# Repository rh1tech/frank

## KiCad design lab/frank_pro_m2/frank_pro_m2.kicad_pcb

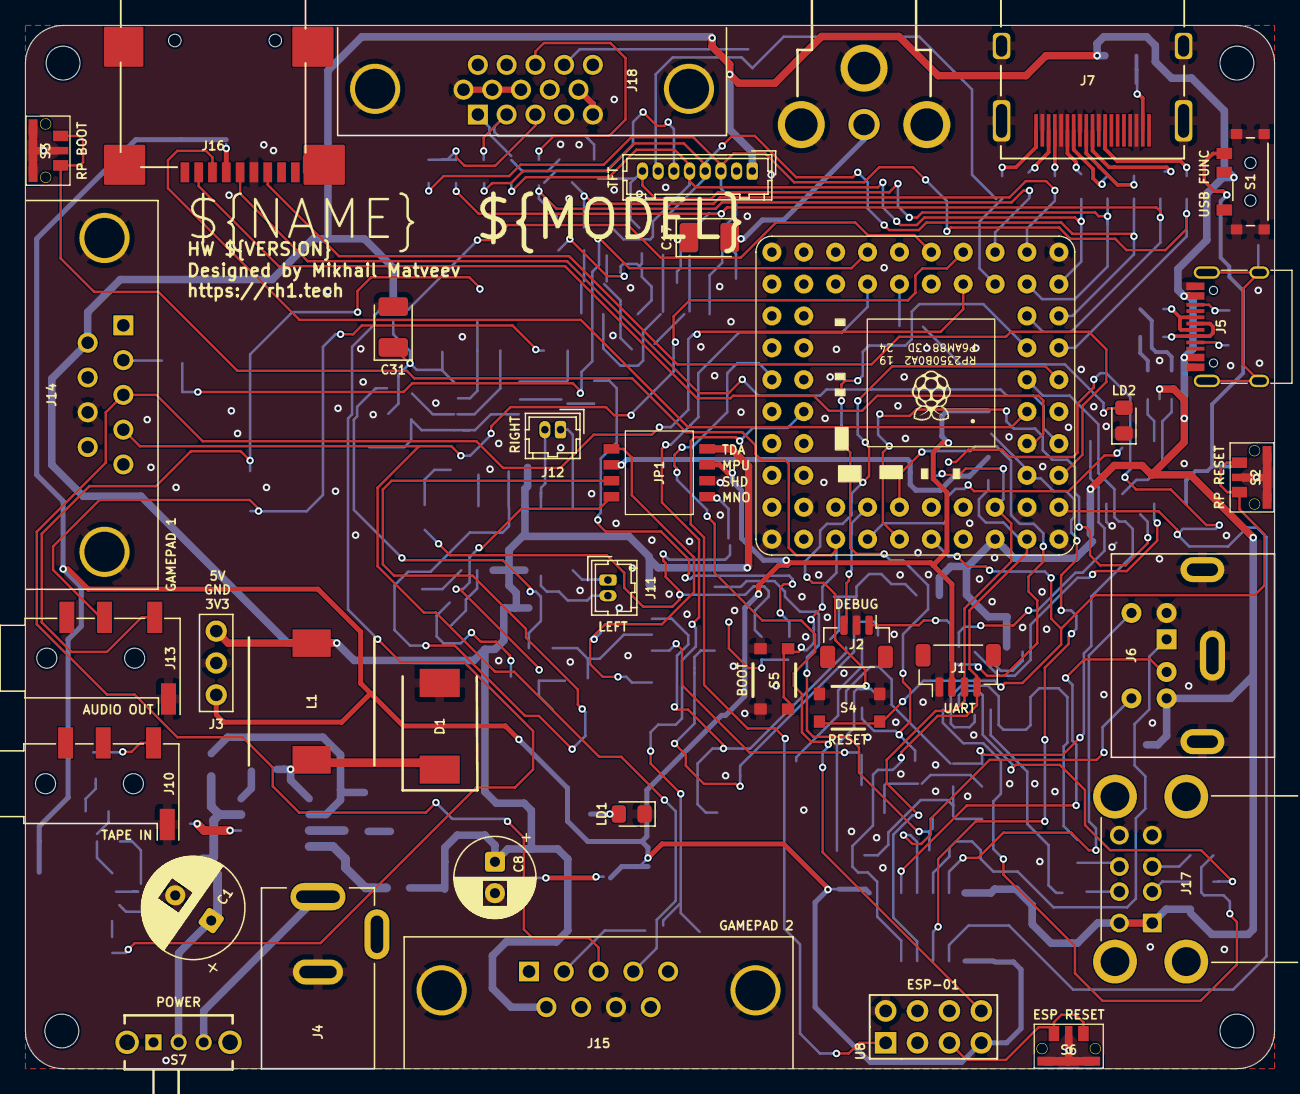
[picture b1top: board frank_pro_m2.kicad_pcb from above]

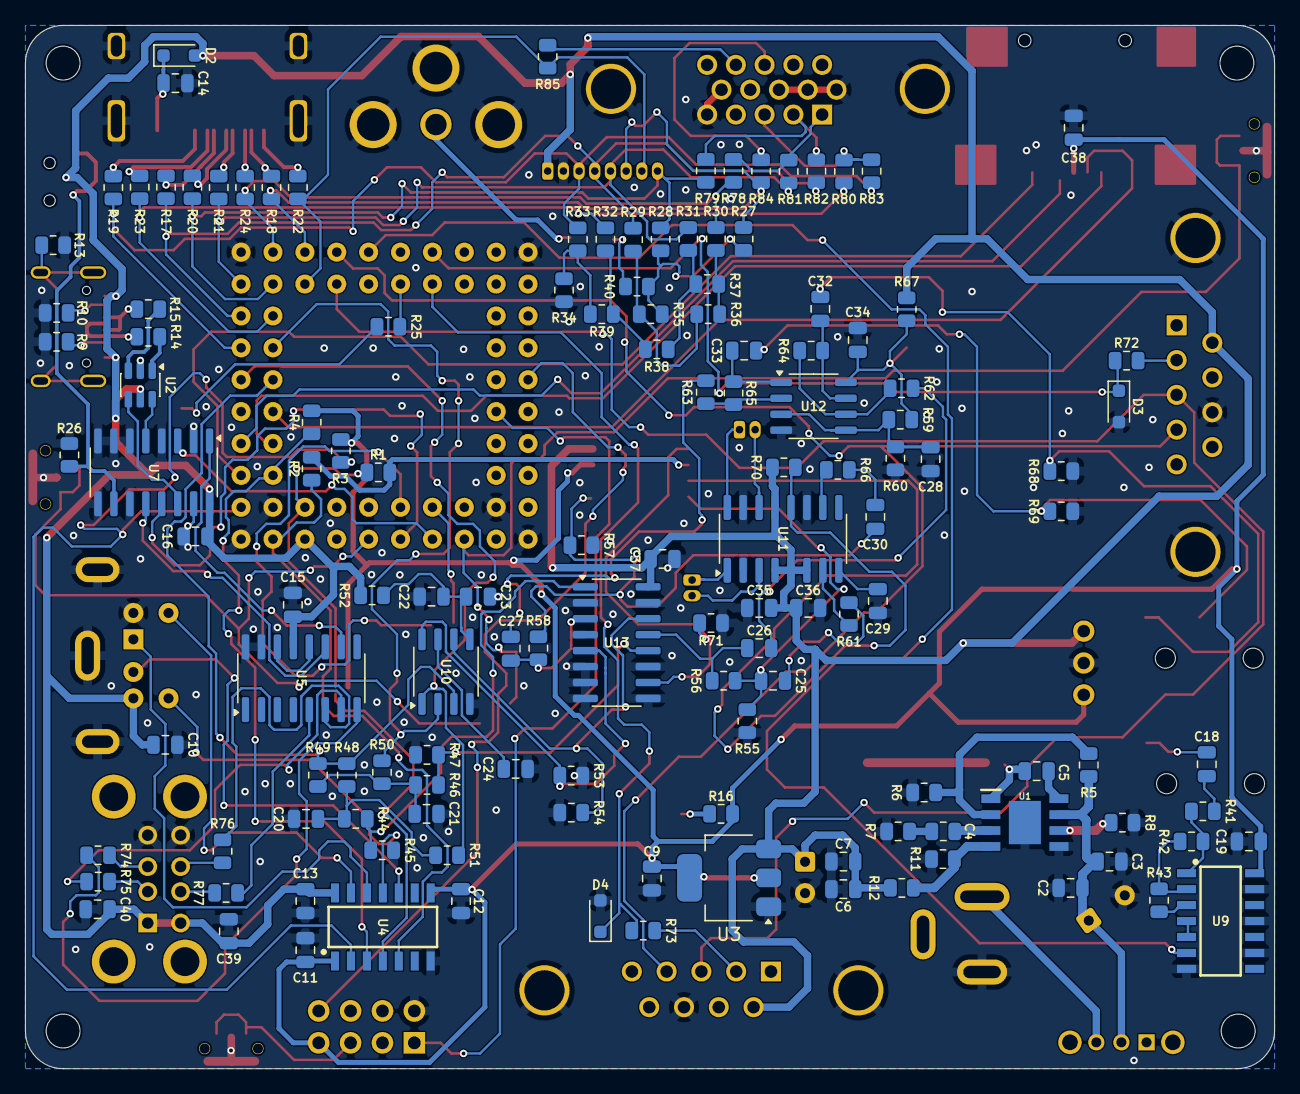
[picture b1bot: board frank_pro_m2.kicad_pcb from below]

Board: 2 copper layers, 99.5 x 83.1 mm, 175 parts (135 on the bottom side), 137 nets.

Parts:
C1: 680u; C_Radial_D8.0mm_P3.50mm
C2, C7, C9, C22, C24, C26, C27, C28, C32, C33, C39, C40: 10u; C_0805_2012Metric
C3, C5, C6, C10, C11, C12, C13, C14, C16, C18, C19, C23, C29, C34, C37, C38: 100n; C_0805_2012Metric
C4: 150pF; R_0805_2012Metric
C8: 220u; C_Radial_D6.3mm_P2.50mm
C15: 4.7u; C_0805_2012Metric
C17: 220u; C_3528_Tantalum
C20, C21: 47n; C_0805_2012Metric
C25, C30, C35: 1u; C_0805_2012Metric
C31: 10u; C_3528_Tantalum
C36: 47u; C_0805_2012Metric
D1: 1N5822; D_SMA_SS34
D2: 1N5819WS; D_SOD-323
D3, D4: 3V3; D_SOD-323
H1, H2, H3, H4: Hole 2.7mm; MountingHole_2.7mm
J1: UART; JST_SH_1x04_P1.00mm_Vertical
J2: DEBUG; JST_SH_1x03_P1.00mm_Vertical
J3: PWR; PinHeader_1x03_P2.54mm
J4: DC-005-5A-2.0; BarrelJack_DC-005
J5: USB4215-03-A; USB_C_Receptacle
J6: MDC-036; MiniDIN_6pin_Female
J7: DC3RX19JA2; HDMI_Female
J8: RCA-103; BarrelJack_RCJ-012
J9: Pin Header 1x08; JST_GH_1x08_P1.25mm
J10, J13: PJ-320D; AudioJack_3.5mm_PJ320D
J11: PAM L; JST_GH_1x02_P1.25mm
J12: PAM R; JST_GH_1x02_P1.25mm
J14, J15: GP2; DSUB-9_Male_TopMount
J16: 104031-0811; MicroSD_SMD_Long
J17: SS-52100-004; USB_A_Stacked
J18: VGA; DSUB-15_Female
JP1: Config Switches; DIPSwitch_4pos_DS05
L1: 22uH; Inductor_CDRH104RNP
LD1: Green; LED_0805
LD2: Blue; LED_0805
R1, R2, R3, R4, R26, R44, R46, R56, R58, R59, R60, R61, R62, R63, R66, R70, R71: 10K; R_0805_2012Metric
R5, R7, R8, R42, R43: 100K; R_0805_2012Metric
R6: 24K; R_0805_2012Metric
R9, R10: 5.1K; R_0805_2012Metric
R11: 8.2K; R_0805_2012Metric
R12: 43K; R_0805_2012Metric
R13: 1M; R_0805_2012Metric
R14, R15, R74, R75, R76, R77: 22R; R_0805_2012Metric
R16, R25, R50, R51, R72, R73, R81, R82, R83: 1K; R_0805_2012Metric
R17, R18, R19, R20, R21, R22, R23, R24, R28, R29, R30, R31, R32, R33: 270R; R_0805_2012Metric
R27: 750R; R_0805_2012Metric
R34: 300R; R_0805_2012Metric
R35, R36, R37, R38, R39: 150R; R_0805_2012Metric
R40: 51R; R_0805_2012Metric
R41: 4.7K; R_0805_2012Metric
R45, R47, R48, R49, R55, R57: 2K; R_0805_2012Metric
R52, R67, R84, R85: 100R; R_0805_2012Metric
R53, R54: 470R; R_0805_2012Metric
R64, R65: 47K; R_0805_2012Metric
R68, R69: 20K; R_0805_2012Metric
R78, R79, R80: 330R; R_0805_2012Metric
S1: MSK12C02; Switch_Slide_MSK12C02
S2: RP Reset; Button_SMD_TS1234VW
S3: RP BOOT; Button_SMD_TS1234VW
S4: RP Reset; Button_SMD_3x4x2mm
S5: RP BOOT; Button_SMD_3x4x2mm
S6: ESP Reset; Button_SMD_TS1234VW
S7: SK12D07VG3NS; Switch_Slide_SK12D07VG3NS
U1: MP1584EN-LF-Z; SOIC-9_P1.27mm
U2: USBLC6-2SC6; SOT-23-6
U3: AMS1117 3.3; SOT-223-3_TabPin2
U4: TXS0104EDR; SOIC-14_P1.27mm
U5: MW7211A; SOP-16_P1.27mm
U6: Pimoroni PGA2350; PGA2350
U7, U13: 74HC4052D; SOP-16_P1.27mm
U8: ESP-01v090; ESP-01S
U9: CD4069UBM; SOIC-14_P1.27mm
U10: TDA1387T; SO-8
U11: PAM8403D; SOP-16_P1.27mm
U12: LM358; SO-8

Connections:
+3V3: C9.1, C11.1, C12.1, C19.1, C38.2, J1.2, J3.1, J16.4 (VDD), JP1.4 (NO_2), R3.2, R4.2, R16.2, U3.2 (VO), U4.1 (VCCA), U4.8 (OE), U8.7 (VCC), U9.14 (VDD)
/AMP_L: C26.1, R56.1, U13.13 (1Z)
/AMP_R: C27.1, R58.1, U13.3 (2Z)
/AUDIOSW: JP1.1 (COM_1), R71.2, U13.10 (S0)
/Audio/AMP_OUTL: C32.2, J13.T, R68.2
/Audio/AMP_OUTR: C33.2, J13.R, R69.2
/Audio/AMP_PAM_OUTL_M: J11.2, U11.3 (-OUTL)
/Audio/AMP_PAM_OUTL_P: J11.1, U11.1 (+OUT_L)
/Audio/AMP_PAM_OUTR_M: J12.2, U11.14 (-OUT_R)
/Audio/AMP_PAM_OUTR_P: J12.1, U11.16 (+OUT_R)
/Composite/CVBS: C17.2, J8.1
/DM: U6.53 (USB_DM), U7.3 (2Z)
/DP: U6.54 (USB_DP), U7.13 (1Z)
/ESP_RST: S6.1, U8.5 (RST)
/ESP_RX: U6.40 (GP38), U8.8 (URXD)
/ESP_TX: U6.41 (GP39), U8.1 (UTXD)
/MONO_L: C25.1, JP1.7 (COM_4), R55.1, R56.2
/MONO_R: C30.1, JP1.8 (NO_4), R57.1, R58.2
/MSPUP3V3: JP1.3 (COM_2), R1.2, R2.2
/PBOOTSEL: S3.1, S5.1, S5.3, U6.51 (BOOTSEL)
/PGPIO0: J1.3, R1.1, U4.4 (A3), U6.61 (GP0)
/PGPIO1: J1.4, R2.1, U4.5 (A4), U6.62 (GP1)
/PGPIO2: R3.1, U4.2 (A1), U6.2 (GP2)
/PGPIO3: R4.1, U4.3 (A2), U6.3 (GP3)
/PGPIO4: J16.7 (DAT0), U6.4 (GP4)
/PGPIO5: J16.2 (DAT3/CD), U6.5 (GP5)
/PGPIO6: J16.5 (CLK), U6.6 (GP6)
/PGPIO7: J16.3 (CMD), U6.7 (GP7)
/PGPIO9: R48.1, R49.1, U6.9 (GP9), U10.3 (DATA)
/PGPIO10: R51.2, U6.10 (GP10), U10.1 (SCLK)
/PGPIO11: R50.2, U6.11 (GP11), U10.2 (LRCK)
/PGPIO12: J9.3, R19.2, R33.1, R83.1, U6.12 (GP12)
/PGPIO13: R23.2, R32.1, R80.1, U6.13 (GP13)
/PGPIO14: J9.4, R17.2, R29.1, R82.1, U6.14 (GP14)
/PGPIO15: J9.8, R20.2, R28.1, R79.1, U6.15 (GP15)
/PGPIO16: J9.5, R21.2, R31.1, R81.1, U6.16 (GP16)
/PGPIO17: R24.2, R30.1, R78.1, U6.17 (GP17)
/PGPIO18: J9.6, R18.2, R27.1, R84.2, U6.19 (GP18)
/PGPIO19: J9.7, R22.2, R85.2, U6.20 (GP19)
/PGPIO20: J14.4, J15.4, U6.21 (GP20)
/PGPIO21: J14.3, J15.3, U6.22 (GP21)
/PGPIO22: U6.23 (GP22), U9.6 (I=*C)
/PGPIO26: D3.1 (K), R72.1, U6.27 (GP26)
/PGPIO27: D4.1 (K), R73.1, U6.28 (GP27)
/PRUN: S2.1, S4.1, S4.3, U6.56 (RUN)
/PS2/KB_CLK_5V: J6.5, U4.13 (B1)
/PS2/KB_DATA_5V: J6.1, U4.12 (B2)
/PS2/MS_CLK_5V: J6.6, U4.11 (B3)
/PS2/MS_DATA_5V: J6.2, U4.10 (B4)
/PSWCLK: J2.1, U6.55 (SWCLK)
/PSWDIO: J2.3, U6.52 (SWDIO)
/PWM_L: R46.2, R47.1, U13.12 (1Y0)
/PWM_R: R44.2, R45.1, U13.1 (2Y0)
/Power/D+: J5.6 (DP1), J5.8 (DP2), R15.2
/Power/D-: J5.5 (DN2), J5.7 (DN1), R14.2
/Power/VBUS_IN: C1.1, C2.1, C3.1, R5.2, S7.2, U1.7 (VIN)
/SHND: JP1.5 (COM_3), R70.2, U11.12 (SHND)
/TC_DM: U2.6 (I/O1), U7.5 (2Y1)
/TC_DP: U2.4 (I/O2), U7.14 (1Y1)
/TDA_L: R54.2, U10.6 (A_LEFT), U13.14 (1Y1)
/TDA_R: R53.1, U10.8 (A_RIGHT), U13.5 (2Y1)
/Tape In/TAPE: C18.2, J10.T
/UH_DM1: R75.1, U5.7 (DM3)
/UH_DM2: R77.1, U5.5 (DM2)
/UH_DM_IN: U5.10 (DMU), U7.1 (2Y0)
/UH_DP1: R74.1, U5.8 (DP3)
/UH_DP2: R76.1, U5.6 (DP2)
/UH_DP_IN: U5.11 (DPU), U7.12 (1Y0)
/UM_SW: R26.2, S1.3, U7.10 (S0)
GND: C1.2, C2.2, C3.2, C6.1, C7.2, C8.2, C9.2, C10.2, C11.2, C12.2, C13.2, C14.2, C15.2, C16.1, C19.2, C20.2, C21.2, C22.2, C23.2, C24.2, C28.1, C29.2, C31.2, C34.1, C35.2, C36.2, C37.1, C38.1, C39.2, C40.2, D1.2 (A), D3.2 (A), D4.2 (A), J1.1, J2.2, J3.2, J4.2, J5.1 (GND), J5.12 (GND), J6.3, J7.2 (G_D2), J7.5 (G_D1), J7.8 (G_D0), J7.11 (G_CLK), J7.17 (G_DDC/CEC), J7.20 (SHIELD1), J7.21 (SHIELD2), J7.22 (SHIELD3), J7.23 (SHIELD4), J8.2, J9.2, J10.S, J13.S, J14.8, J15.8, J16.6 (VSS), J17.4 (GND1), J17.8 (GND2), J18.0, J18.5, J18.6, J18.7, J18.8, J18.10, JP1.6 (NO_3), LD1.1 (K), LD2.1 (K), R6.2, R7.2, R8.2, R9.1, R10.1, R11.1, R13.1, R26.1, R34.1, R45.2, R47.2, R53.2, R54.1, R55.2, R57.2, R60.1, R68.1, R69.1, R71.1, S1.4_1 (GND), S1.4_2 (GND), S1.4_3 (GND), S1.4_4 (GND), S2.2, S2.3 (GND), S3.2, S3.3 (GND), S4.2, S4.4, S5.2, S5.4, S6.2, S6.3 (GND), U1.5 (GND), U1.9 (EP), U2.2 (GND), U3.1 (GND), U4.7 (GND), U5.15 (GND), U5.16 (GND), U6.1 (GND), U6.18 (GND), U6.33 (GND), U6.48 (GND), U7.2 (2Y2), U7.4 (2Y3), U7.6 (~E), U7.7 (VEE), U7.8 (GND), U7.9 (S1), U7.11 (1Y3), U7.15 (1Y2), U8.2 (GND), U9.7 (VSS), U9.9 (D14), U9.11 (E), U9.13 (F), U10.4 (AGND), U11.2 (PGND), U11.11 (GND), U11.15 (PGND), U12.4 (V-), U13.2 (2Y2), U13.4 (2Y3), U13.6 (~E), U13.7 (VEE), U13.8 (GND), U13.9 (S1), U13.11 (1Y3), U13.15 (1Y2)
GP25: R25.2, U6.26 (GP25)
unnamed: C4.2, R7.1
unnamed: C17.1, R40.2
unnamed: C18.1, R41.2
unnamed: C20.1, R44.1, R48.2, R51.1
unnamed: C21.1, R46.1, R49.2, R50.1
unnamed: C25.2, R61.2
unnamed: C26.2, R62.2
unnamed: C27.2, R63.2
unnamed: C30.2, R66.2
unnamed: C32.1, R64.1, U12.7
unnamed: C33.1, R65.1, U12.1
unnamed: C5.2, D1.1 (K), L1.1, U1.1 (SW)
unnamed: C14.1, D2.1 (K), J7.18 (+5V)
unnamed: J4.1, S7.3
unnamed: J5.4 (CC1), R9.2
unnamed: J5.10 (CC2), R10.2
unnamed: J5.13 (SHIELD), R13.2
unnamed: J7.12 (CLKN), R19.1
unnamed: J7.10 (CLKP), R23.1
unnamed: J7.9 (D0N), R17.1
unnamed: J7.7 (D0P), R20.1
unnamed: J7.6 (D1N), R21.1
unnamed: J7.4 (D1P), R24.1
unnamed: J7.3 (D2N), R18.1
unnamed: J7.1 (D2P), R22.1
unnamed: J14.2, R72.2
unnamed: J15.2, R73.2
unnamed: J17.3 (D1+), R74.2
unnamed: J17.2 (D1-), R75.2
unnamed: J17.7 (D2+), R76.2
unnamed: J17.6 (D2-), R77.2
unnamed: J18.1, R78.2, R81.2
unnamed: J18.2, R79.2, R82.2
unnamed: J18.3, R80.2, R83.2
unnamed: J18.13, R84.1
unnamed: J18.14, R85.1
unnamed: LD1.2 (A), R16.1
unnamed: LD2.2 (A), R25.1
unnamed: R14.1, U2.1 (I/O1)
unnamed: R15.1, U2.3 (I/O2)
unnamed: R27.2, R28.2, R35.2, R40.1
unnamed: R29.2, R35.1, R36.2
unnamed: R30.2, R36.1, R37.2
unnamed: R31.2, R37.1, R38.2
unnamed: R32.2, R38.1, R39.2
unnamed: R33.2, R34.2, R39.1
unnamed: C5.1, U1.8 (BST)
unnamed: C4.1, U1.3 (COMP)
unnamed: R5.1, R6.1, U1.2 (EN)
unnamed: R11.2, R12.2, U1.4 (FB)
unnamed: R8.1, U1.6 (FREQ)
unnamed: U5.12 (VD33), U5.14 (VD3)
unnamed: R41.1, R42.2, U9.1 (A)
unnamed: R43.1, U9.3 (B)
unnamed: U9.4 (H=*B), U9.5 (C)
unnamed: R42.1, R43.2, U9.2 (G-*A)
unnamed: C24.1, U10.7 (FLT)
unnamed: C22.1, C23.1, R52.1, U10.5 (VA)
unnamed: R61.1, U11.7 (INL)
unnamed: R66.1, U11.10 (INR)
unnamed: C29.1, U11.8 (VREF)
unnamed: C28.2, R59.1, R60.2, U12.3 (+), U12.5 (+)
unnamed: R63.1, R65.2, U12.2 (-)
unnamed: R62.1, R64.2, U12.6 (-)
unnamed: C31.1, C34.2, R59.2, R67.2, U12.8 (V+)
VBUS: C6.2, C7.1, C8.1, C10.1, C13.1, C15.1, C16.2, C35.1, C36.1, C37.2, C39.1, C40.1, D2.2 (A), J3.3, J5.2 (VBUS), J5.11 (VBUS), J6.4, J9.1, J14.6, J15.6, J17.1 (VBUS1), J17.5 (VBUS2), JP1.2 (NO_1), L1.2, R12.1, R52.2, R67.1, R70.1, S1.2, U2.5 (VBUS), U3.3 (VI), U4.14 (VCCB), U5.13 (VDD5), U6.60 (VBUS), U7.16 (VCC), U11.4 (PVDD), U11.5 (MUTE), U11.6 (VDD), U11.13 (PVDD), U13.16 (VCC)

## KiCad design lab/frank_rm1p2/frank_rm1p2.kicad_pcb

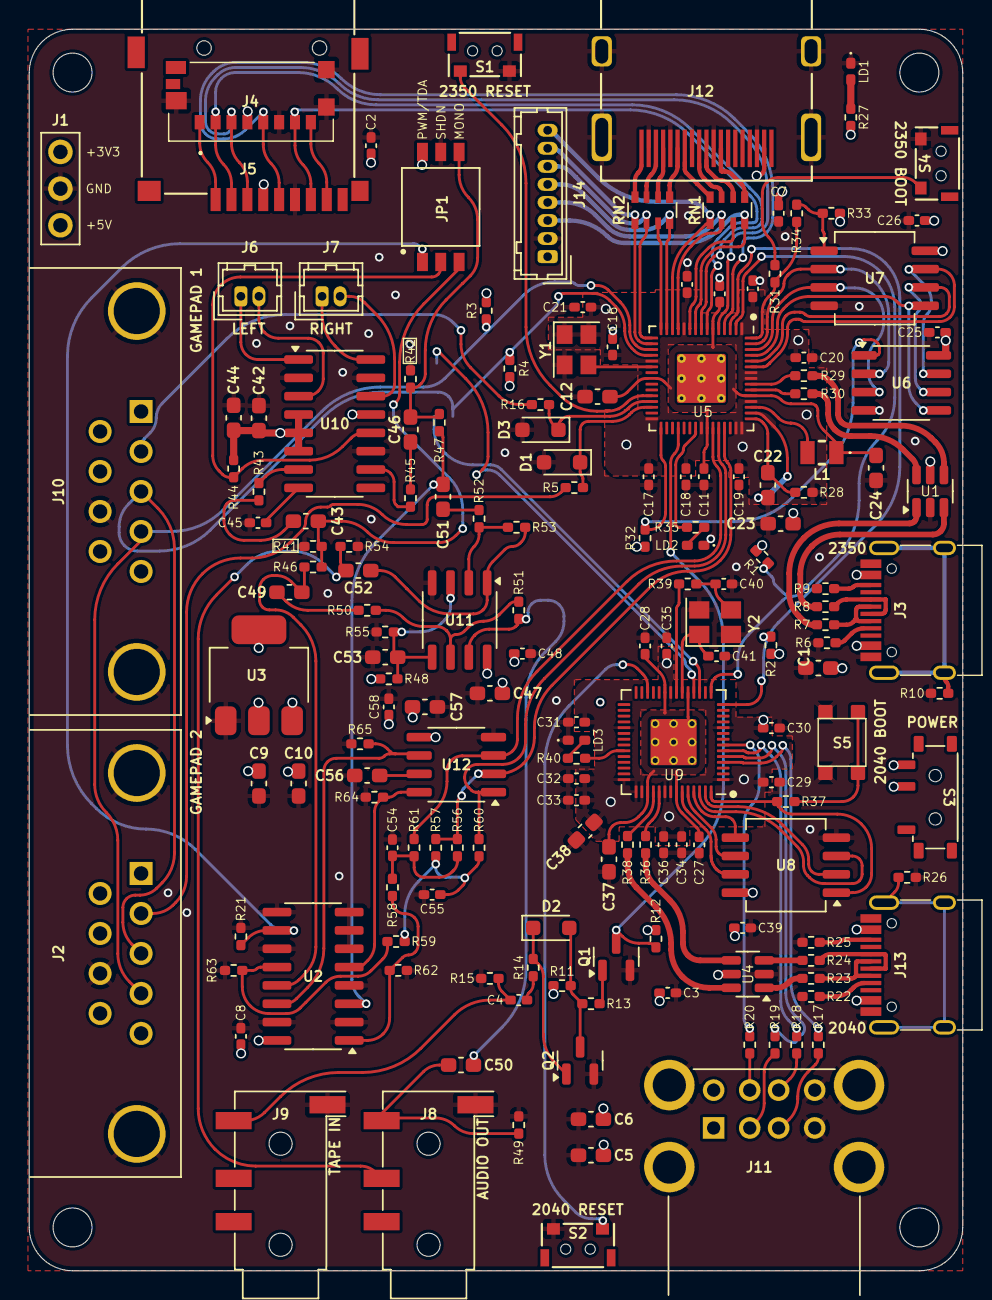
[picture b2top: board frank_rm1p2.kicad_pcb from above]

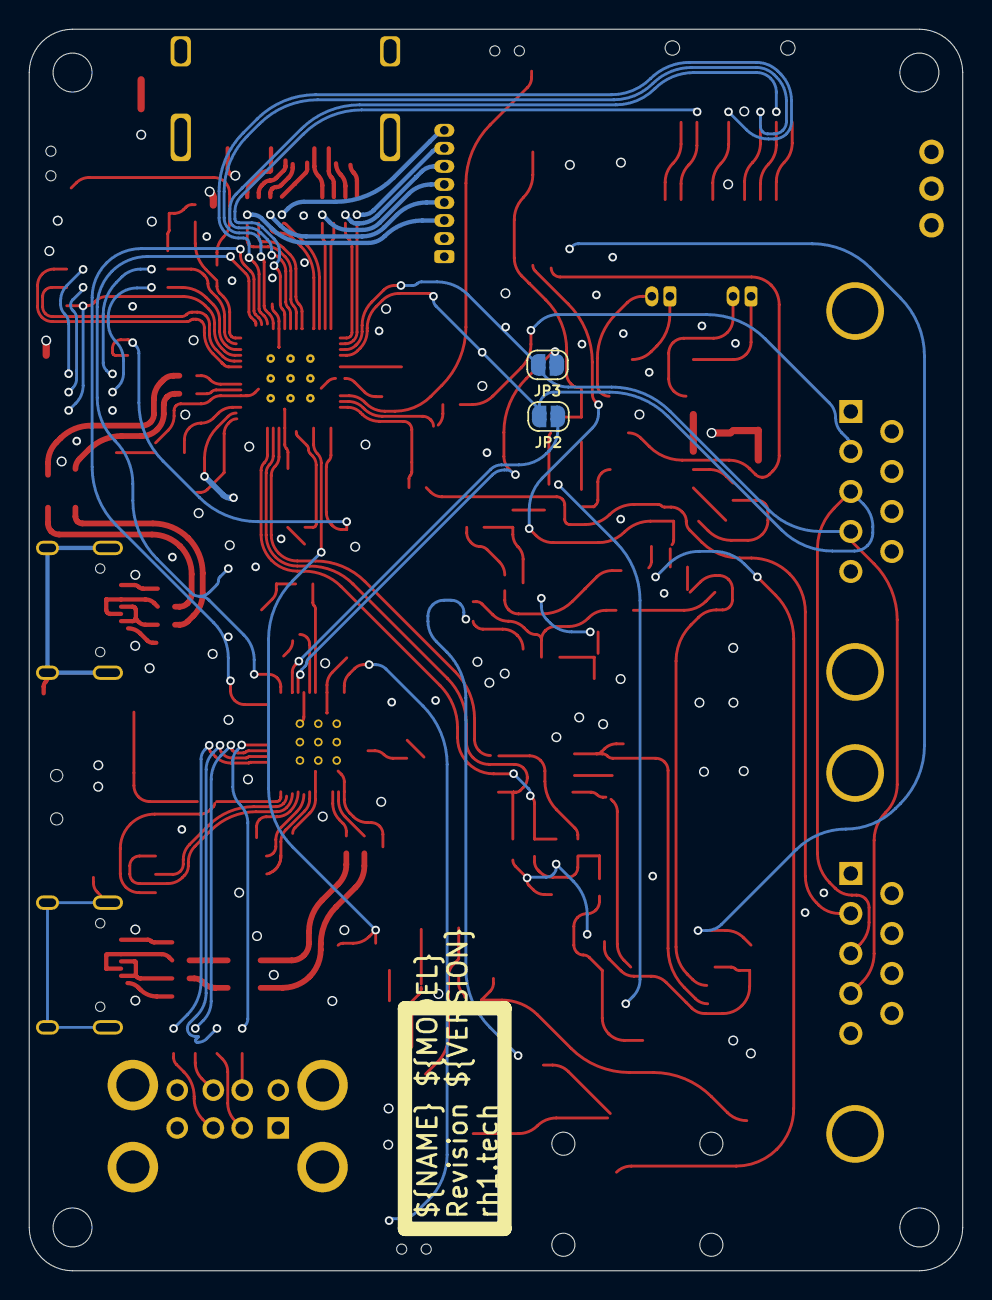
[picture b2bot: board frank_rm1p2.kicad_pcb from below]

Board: 4 copper layers, 64.7 x 86.0 mm, 174 parts (2 on the bottom side), 137 nets.

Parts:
C1, C5, C6, C9, C10, C47, C49, C50, C51, C52, C53, C56, C57: 10u; Capacitor (0603)
C2, C3, C4, C7, C8, C11, C13, C14, C15, C16, C17, C18, C19, C20, C21, C25, C26, C27, C28, C29, C30, C31, C32, C33, C34, C35, C36, C39, C45, C48, C58: 100n; Capacitor (0402)
C12, C22, C23, C24: 4.7u; Capacitor (0603)
C37, C38, C42, C43, C46: 1u; Capacitor (0603)
C40, C41: 15p; Capacitor (0402)
C44: 47u; Capacitor (0603)
C54, C55: 47n; Capacitor (0402)
D1, D3: 3V3; Diode (SOD-323)
D2: 1N4148; Diode (SOD-323)
H1, H2, H3, H4: MountingHole; Mounting Hole (2.7mm)
J1: PWR; Pin Header (1x03)
J2, J10: D-SUB 9 Male; D-SUB (9 pin, male, top mount)
J3, J13: USB4215-03-A; USB Type C
J4: 0475710001; MicroSD (SMD, short)
J5: 104031-0811; MicroSD (SMD, long)
J6: PAM L; Connector Female 1.25 JST 2P
J7: PAM R; Connector Female 1.25 JST 2P
J8, J9: PJ-320D; Jack (3.5mm, PJ-320D)
J11: SS-52100-004; USB Type A (stacked)
J12: DC3RX19JA2; HDMI (female)
J14: Pin Header 1x08; Connector Female 1.25 JST 8P
JP1: Main Jumpers; SW_DS05-127-2-03BK-SMT-TR
JP2: Mouse (DATA); Jumper (solder)
JP3: Mouse (CLK); Jumper (solder)
L1: 3.3u; Inductor (0806)
LD1: Power; LED (0402)
LD2, LD3: Blue; LED (0402)
Q1, Q2: BC850; SOT-23
R1, R2, R3, R4, R11, R13, R14, R21, R32, R33, R43, R44, R45, R46, R47, R48, R50, R52, R55, R58, R59: 10K; Resistor (0402)
R5, R12, R16, R27, R31, R35, R37, R39, R40, R60, R61: 1K; Resistor (0402)
R6, R9, R22, R25: 5.1K; Resistor (0402)
R7, R8, R17, R18, R19, R20, R23, R24: 22R; Resistor (0402)
R10, R26: 1M; Resistor (0402)
R15: 100R; Resistor (0402)
R28: 33R; Resistor (0402)
R29, R30, R36, R38: 27R; Resistor (0402)
R34: 0R; Resistor (0402)
R41, R42, R56, R57, R62, R63: 2K; Resistor (0402)
R49, R54: 20K; Resistor (0402)
R51, R53: 47K; Resistor (0402)
R64, R65: 470R; Resistor (0402)
RN1, RN2: 270R; Resistor Array (4x0603)
S1: Reset RP2530A; TACT-SIDE-4623
S2: Reset RP2040; TACT-SIDE-4623
S3: MSK12C02; Switch (MSK12C02)
S4: Boot 2350; TACT-SIDE-4623
S5: Boot 2040; Button (SMD, 3x3mm, 1-1)
U1, U4: USBLC6-2SC6; SOT-23-6
U2: 74HC4052D; SOP-16
U3: NCP1117 3.3; SOT-223
U5: RP2350; QFN 60 (RP2350A)
U6: ESP-PSRAM32; SO-8
U7: W25Q128JVS; SOIC-8
U8: W25Q128JVSIQ; SOIC-8
U9: RP2040; QFN 56
U10: PAM8403D; SOP-16
U11: LM358; SO-8
U12: TDA1387T; SO-8
Y1: ASE-12MHz; Crystal (3225, active)
Y2: 12 MHz; Crystal (3225)

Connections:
+1V1: C11.1, C12.1, C13.1, C24.1, L1.1, U5.6 (DVDD), U5.23 (DVDD), U5.39 (DVDD), U5.50 (VREG_FB)
+3V3: C2.2, C3.1, C8.2, C9.1, C14.1, C15.1, C16.1, C17.1, C18.1, C19.1, C20.1, C21.1, C23.1, C25.1, C26.1, C29.1, C30.1, C31.1, C32.1, C33.1, C34.1, C35.1, C36.1, C38.1, C39.1, J1.1, J4.P4 (VDD), J5.4 (VDD), R1.2, R2.2, R3.2, R4.2, R11.1, R12.1, R27.2, R28.1, R32.2, R33.1, U2.16 (VCC), U3.2 (VO), U5.1 (IOVDD), U5.11 (IOVDD), U5.20 (IOVDD), U5.30 (IOVDD), U5.38 (IOVDD), U5.44 (ADC_AVDD), U5.45 (IOVDD), U5.49 (VREG_VIN), U5.53 (USB_OTP_VDD), U5.54 (QSPI_IOVDD), U6.8 (VCC), U7.8 (VCC), U8.8 (VCC), U9.1 (IOVDD), U9.10 (IOVDD), U9.22 (IOVDD), U9.33 (IOVDD), U9.42 (IOVDD), U9.43 (ADC_AVDD), U9.44 (VREG_IN), U9.48 (USB_VDD), U9.49 (IOVDD), Y1.1 (EN), Y1.4 (Vdd)
/AMP_IN_L: C49.1, R46.1, U2.13 (1Z)
/AMP_IN_R: C51.1, R47.1, U2.3 (2Z)
/AUDIOSW: JP1.1, R21.2, U2.10 (S0)
/Audio Out/AMP_OUTL: C50.2, J8.T, R49.2
/Audio Out/AMP_OUTR: C52.2, J8.R, R54.2
/Audio Out/AMP_PAM_OUTL_M: J6.2, U10.3 (-OUTL)
/Audio Out/AMP_PAM_OUTL_P: J6.1, U10.1 (+OUT_L)
/Audio Out/AMP_PAM_OUTR_M: J7.2, U10.14 (-OUT_R)
/Audio Out/AMP_PAM_OUTR_P: J7.1, U10.16 (+OUT_R)
/D+: R29.1, U1.4 (I/O2)
/D-: R30.1, U1.6 (I/O1)
/DAT1: J4.P8 (DAT1), J5.8 (DAT1)
/DAT2: J4.P1 (DAT2), J5.1 (DAT2)
/GPIO0: R1.1, U5.2 (GPIO0), U9.15 (GPIO12)
/GPIO1: R2.1, U5.3 (GPIO1), U9.14 (GPIO11)
/GPIO2: J4.P5 (CLK), J5.5 (CLK), U5.4 (GPIO2)
/GPIO3: J4.P3 (CMD), J5.3 (CMD), U5.5 (GPIO3)
/GPIO4: J4.P7 (DAT0), J5.7 (DAT0), U5.7 (GPIO4)
/GPIO5: J4.P2 (CD/DAT3), J5.2 (DAT3/CD), U5.8 (GPIO5)
/GPIO6: J14.3, RN1.4 (R4.1), U5.9 (GPIO6)
/GPIO7: RN1.3 (R3.1), U5.10 (GPIO7)
/GPIO8: J14.4, RN1.2 (R2.1), U5.12 (GPIO8)
/GPIO9: J14.8, RN1.1 (R1.1), U5.13 (GPIO9)
/GPIO10: J14.5, RN2.4 (R4.1), U5.14 (GPIO10)
/GPIO11: RN2.3 (R3.1), U5.15 (GPIO11)
/GPIO12: J14.6, RN2.2 (R2.1), U5.16 (GPIO12)
/GPIO13: J14.7, RN2.1 (R1.1), U5.17 (GPIO13)
/GPIO14: J2.4, J10.4, JP3.2 (B), R3.1, U5.18 (GPIO14)
/GPIO15: J2.3, J10.3, JP2.2 (B), R4.1, U5.19 (GPIO15)
/GPIO16: D3.1 (K), R16.1, U5.27 (GPIO16)
/GPIO17: D1.1 (K), R5.1, U5.28 (GPIO17)
/GPIO19: R32.1, U5.31 (GPIO19), U6.1 (~CE)
/GPIO22: Q1.3 (C), R12.2, U5.34 (GPIO22)
/GPIO26: R61.2, U5.40 (GPIO26_ADC0), U12.3 (DATA)
/GPIO27: R60.2, U5.41 (GPIO27_ADC1), U12.1 (SCLK)
/GPIO28: R56.1, R57.1, U5.42 (GPIO28_ADC2), U12.2 (LRCK)
/MONO_L: C43.1, JP1.3, R41.1, R46.2
/MONO_R: C46.1, JP1.4, R42.1, R47.2
/MS_CLK: JP3.1 (A), U9.18 (GPIO15)
/MS_DATA: JP2.1 (A), U9.17 (GPIO14)
/PWM_OUT_L: R59.2, R63.1, U2.12 (1Y0)
/PWM_OUT_R: R58.2, R62.1, U2.1 (2Y0)
/RP2_D+: R36.1, U4.4 (I/O2)
/RP2_D-: R38.1, U4.6 (I/O1)
/RP2_GPIO2: R17.1, U9.4 (GPIO2)
/RP2_GPIO3: R19.1, U9.5 (GPIO3)
/RP2_GPIO4: R18.1, U9.6 (GPIO4)
/RP2_GPIO5: R20.1, U9.7 (GPIO5)
/RP2_RUN: S2.1, U9.26 (RUN)
/RP2040/GPIO25: R40.2, U9.37 (GPIO25)
/RP2040/QSPI_SCLK: U8.6 (CLK), U9.52 (QSPI_SCLK)
/RP2040/QSPI_SD0: U8.5 (DI(IO0)), U9.53 (QSPI_SD0)
/RP2040/QSPI_SD1: U8.2 (DO(IO1)), U9.55 (QSPI_SD1)
/RP2040/QSPI_SD2: U8.3 (IO2), U9.54 (QSPI_SD2)
/RP2040/QSPI_SD3: U8.7 (IO3), U9.51 (QSPI_SD3)
/RP2040/QSPI_SS: R37.1, U8.1 (~CS), U9.56 (QSPI_SS)
/RP2040/XIN: C41.1, U9.20 (XIN), Y2.1
/RP2040/XOUT: R39.1, U9.21 (XOUT)
/RP2350A/FLASH_SS: R33.2, R34.2, U7.1 (~CS)
/RP2350A/QSPI_SCLK: U5.56 (QSPI_SCLK), U6.6 (SCLK), U7.6 (CLK)
/RP2350A/QSPI_SD0: U5.57 (QSPI_SD0), U6.5 (SI/SIO), U7.5 (DI(IO0))
/RP2350A/QSPI_SD1: U5.59 (QSPI_SD1), U6.2 (SO/SIO), U7.2 (DO(IO1))
/RP2350A/QSPI_SD2: U5.58 (QSPI_SD2), U6.3 (SIO2), U7.3 (IO2)
/RP2350A/QSPI_SD3: U5.55 (QSPI_SD3), U6.7 (SIO3), U7.7 (IO3)
/RP2350A/QSPI_SS: R31.1, R34.1, U5.60 (QSPI_SS)
/RP2350A/VREG_AVDD: C22.1, R28.2, U5.46 (VREG_AVDD)
/RP2350A/VREG_LX: L1.2, U5.48 (VREG_LX)
/RP2350A/XIN: U5.21 (XIN), Y1.3 (OUT)
/RP2350A/~USB_BOOT: R31.2, S4.2
/RUN: S1.1, U5.26 (RUN)
/SHND: JP1.2, R44.2, U10.12 (SHND)
/TDA_L: R65.2, U2.14 (1Y1), U12.6 (A_LEFT)
/TDA_R: R64.1, U2.5 (2Y1), U12.8 (A_RIGHT)
GND: C1.2, C2.1, C3.2, C5.2, C6.2, C7.2, C8.1, C9.2, C10.2, C11.2, C12.2, C13.2, C14.2, C15.2, C16.2, C17.2, C18.2, C19.2, C20.2, C21.2, C22.2, C23.2, C24.2, C25.2, C26.2, C27.2, C28.2, C29.2, C30.2, C31.2, C32.2, C33.2, C34.2, C35.2, C36.2, C37.2, C38.2, C39.2, C40.2, C41.2, C42.2, C44.2, C45.2, C47.1, C48.1, C53.1, C54.2, C55.2, C56.2, C57.2, C58.2, D1.2 (A), D3.2 (A), J1.2, J2.8, J3.1 (GND), J3.12 (GND), J4.G1 (GND_1), J4.G2 (GND_2), J4.G3 (GND_3), J4.P6 (VSS), J5.6 (VSS), J8.S, J9.S, J10.8, J11.4 (GND1), J11.8 (GND2), J11.9 (Shield), J12.2 (G_D2), J12.5 (G_D1), J12.8 (G_D0), J12.11 (G_CLK), J12.17 (G_DDC/CEC), J12.20 (SHIELD1), J12.21 (SHIELD2), J12.22 (SHIELD3), J12.23 (SHIELD4), J13.1 (GND), J13.12 (GND), J14.2, JP1.5, LD1.1 (K), LD2.1 (K), LD3.1 (K), Q1.2 (E), Q2.2 (E), R6.1, R9.1, R10.2, R15.2, R21.1, R22.1, R25.1, R26.2, R41.2, R42.2, R49.1, R54.1, R55.1, R62.2, R63.2, R64.2, R65.1, S1.2, S2.2, S4.1, S5.2, U1.2 (GND), U2.2 (2Y2), U2.4 (2Y3), U2.6 (~E), U2.7 (VEE), U2.8 (GND), U2.9 (S1), U2.11 (1Y3), U2.15 (1Y2), U3.1 (GND), U4.2 (GND), U5.47 (VREG_PGND), U5.61 (GND), U6.4 (VSS), U7.4 (GND), U8.4 (GND), U9.19 (TESTEN), U9.57 (GND), U10.2 (PGND), U10.11 (GND), U10.15 (PGND), U11.4 (V-), U12.4 (AGND), Y1.2 (GND), Y2.2, Y2.4
GPIO25: R35.2, U5.37 (GPIO25)
unnamed: C4.1, J9.T, R15.1
unnamed: C4.2, R14.1
unnamed: C40.1, R39.2, Y2.3
unnamed: C43.2, R43.2
unnamed: C46.2, R45.2
unnamed: C49.2, R50.2
unnamed: C50.1, R51.1, U11.7
unnamed: C51.2, R52.2
unnamed: C52.1, R53.1, U11.1
unnamed: C54.1, R56.2, R58.1, R61.1
unnamed: C55.1, R57.2, R59.1, R60.1
unnamed: D2.2 (A), Q2.3 (C), R11.2, R13.1
unnamed: D2.1 (K), Q2.1 (B), R14.2
unnamed: J2.2, R5.2
unnamed: J3.4 (CC1), R6.2
unnamed: J3.10 (CC2), R9.2
unnamed: J3.5 (DN2), J3.7 (DN1), R7.2
unnamed: J3.6 (DP1), J3.8 (DP2), R8.2
unnamed: J3.13 (SHIELD), R10.1
unnamed: J10.2, R16.2
unnamed: J11.3 (D1+), R17.2
unnamed: J11.2 (D1-), R19.2
unnamed: J11.7 (D2+), R18.2
unnamed: J11.6 (D2-), R20.2
unnamed: J12.12 (CLKN), RN1.5 (R4.2)
unnamed: J12.10 (CLKP), RN1.6 (R3.2)
unnamed: J12.9 (D0N), RN1.7 (R2.2)
unnamed: J12.7 (D0P), RN1.8 (R1.2)
unnamed: J12.6 (D1N), RN2.5 (R4.2)
unnamed: J12.4 (D1P), RN2.6 (R3.2)
unnamed: J12.3 (D2N), RN2.7 (R2.2)
unnamed: J12.1 (D2P), RN2.8 (R1.2)
unnamed: J13.4 (CC1), R22.2
unnamed: J13.10 (CC2), R25.2
unnamed: J13.5 (DN2), J13.7 (DN1), R23.2
unnamed: J13.6 (DP1), J13.8 (DP2), R24.2
unnamed: J13.13 (SHIELD), R26.1
unnamed: LD1.2 (A), R27.1
unnamed: LD2.2 (A), R35.1
unnamed: LD3.2 (A), R40.1
unnamed: Q1.1 (B), R13.2
unnamed: R7.1, U1.1 (I/O1)
unnamed: R8.1, U1.3 (I/O2)
unnamed: R23.1, U4.1 (I/O1)
unnamed: R24.1, U4.3 (I/O2)
unnamed: R37.2, S5.1
unnamed: J13.2 (VBUS), J13.11 (VBUS), S3.2 (B)
unnamed: R30.2, U5.51 (USB_DM)
unnamed: R29.2, U5.52 (USB_DP)
unnamed: R38.2, U9.46 (USB_DM)
unnamed: R36.2, U9.47 (USB_DP)
unnamed: C27.1, C28.1, C37.1, U9.23 (DVDD), U9.45 (VREG_VOUT), U9.50 (DVDD)
unnamed: R43.1, U10.7 (INL)
unnamed: R45.1, U10.10 (INR)
unnamed: C45.1, U10.8 (VREF)
unnamed: C53.2, R48.1, R55.2, U11.3 (+), U11.5 (+)
unnamed: R52.1, R53.2, U11.2 (-)
unnamed: R50.1, R51.2, U11.6 (-)
unnamed: C56.1, U12.7 (FLT)
VBUS: C1.1, C5.1, C6.1, C7.1, C10.1, C42.1, C44.1, C47.2, C48.2, C57.1, C58.1, J1.3, J2.6, J3.2 (VBUS), J3.11 (VBUS), J10.6, J11.1 (VBUS1), J11.5 (VBUS2), J12.18 (+5V), J14.1, JP1.6, R44.1, R48.2, S3.3 (A), U1.5 (VBUS), U3.3 (VI), U4.5 (VBUS), U10.4 (PVDD), U10.5 (MUTE), U10.6 (VDD), U10.13 (PVDD), U11.8 (V+), U12.5 (VA)
